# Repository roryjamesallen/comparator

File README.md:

# comparator
#### A simple dual comparator in Eurorack format.
  
Inputs between +12V and -12V can be compared, and an output of 0 or 5V will be produced accordingly, indicated by the LED.
  
The voltage to compare input A against is controlled by the knob, and is be default 0-12V. However, this voltage can be replaced by plugging a jack into input B, in which case the knob will attenuate this input.

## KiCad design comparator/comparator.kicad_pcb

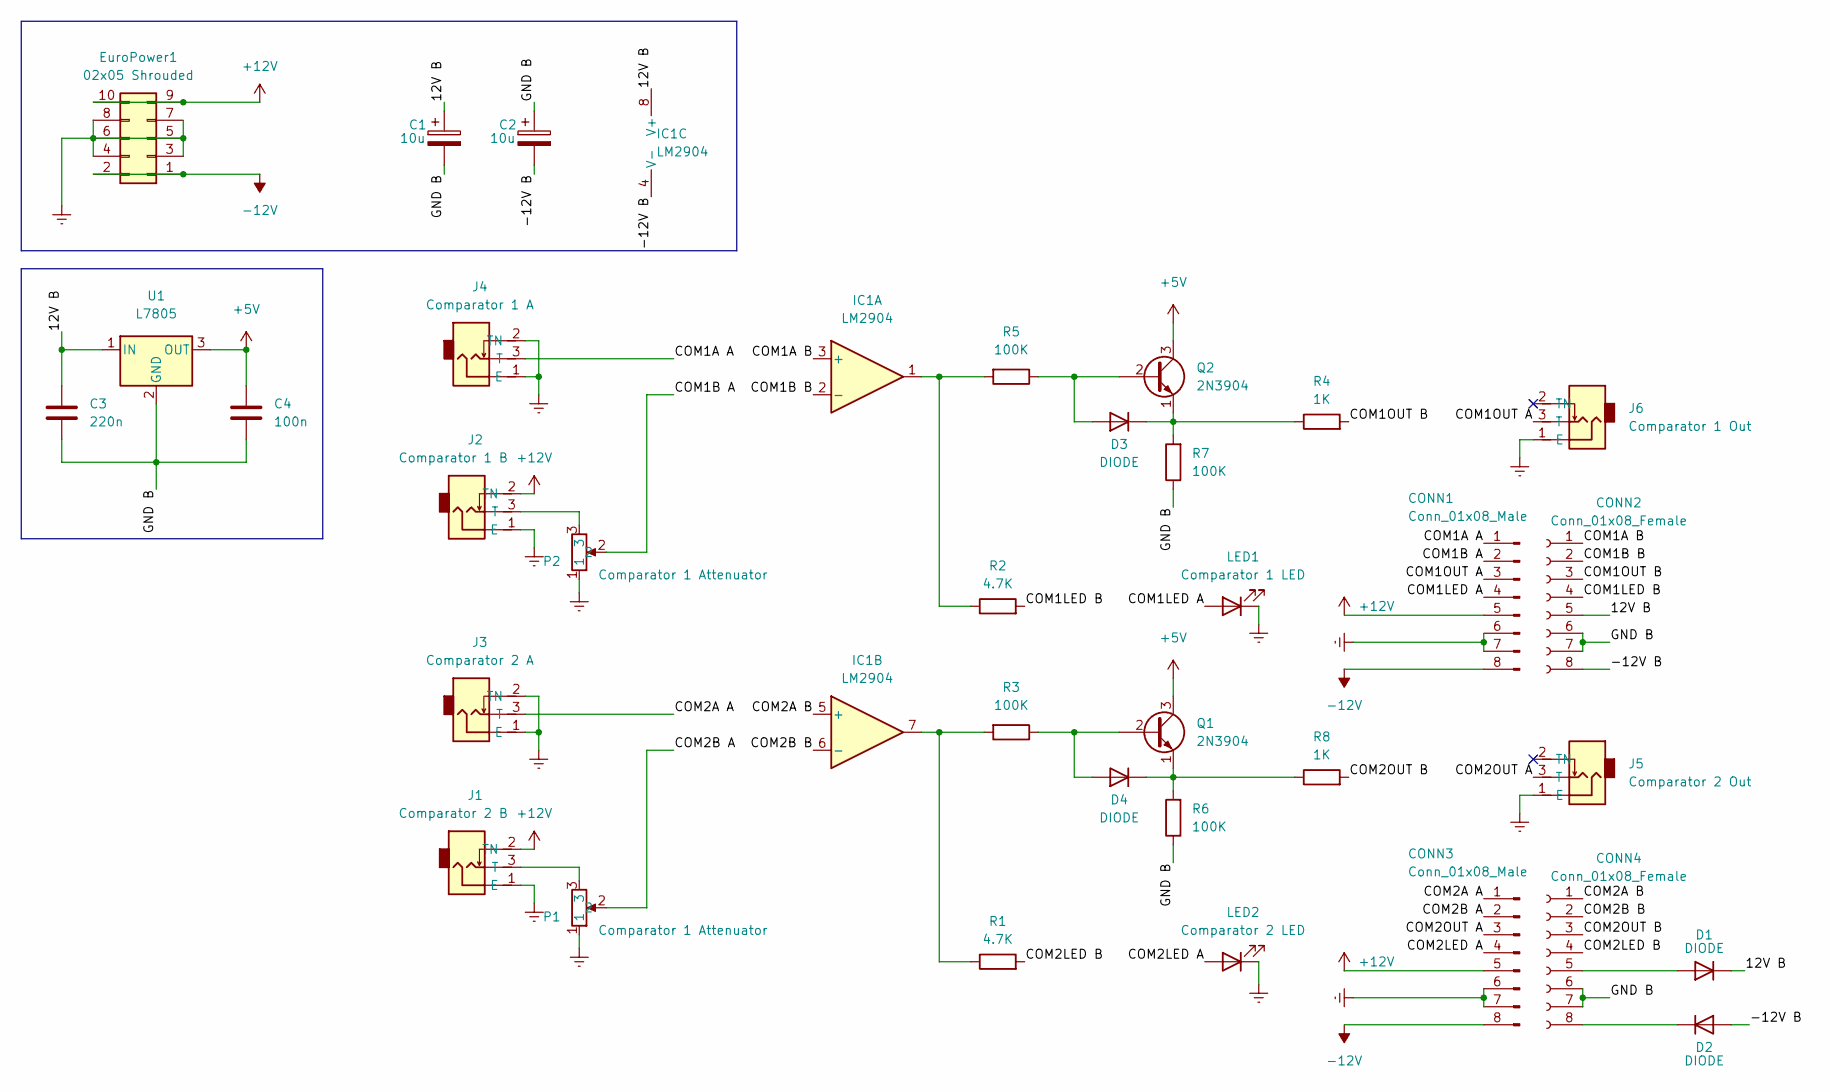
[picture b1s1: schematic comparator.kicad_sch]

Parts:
C1, C2: 10u; CP_Radial_D5.0mm_P2.50mm
C3: 220n; Capacitor Small Non-Polarised
C4: 100n; Capacitor Small Non-Polarised
CONN1, CONN3: Conn_01x08_Male; PinHeader_2x04_P2.54mm_Vertical
CONN2, CONN4: Conn_01x08_Female; PinSocket_2x04_P2.54mm_Vertical
D1, D2: DIODE; D_A-405_P7.62mm_Horizontal
D3, D4: DIODE; Schottky Diode
EuroPower1: 02x05 Shrouded; Eurorack Power Header Unlabeled
IC1: LM2904; DIP-8 IC Socket
J1: Comparator 2 B; Thonkiconn Mono Jack
J2: Comparator 1 B; Thonkiconn Mono Jack
J3: Comparator 2 A; Thonkiconn Mono Jack
J4: Comparator 1 A; Thonkiconn Mono Jack
J5: Comparator 2 Out; Thonkiconn Mono Jack
J6: Comparator 1 Out; Thonkiconn Mono Jack
LED1: Comparator 1 LED; LED 3mm
LED2: Comparator 2 LED; LED 3mm
P1, P2: Comparator 1 Attenuator; Potentiometer 9mm Vertical Linear
Q1, Q2: 2N3904; TO-92_Inline
R1, R2: 4.7K; Resistor 0.25W Through-Hole Short
R3, R5, R6, R7: 100K; Resistor 0.25W Through-Hole Short
R4, R8: 1K; Resistor 0.25W Through-Hole Short
U1: L7805; TO-92

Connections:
+5V: C4.1, Q1.3 (C), Q2.3 (C), U1.3 (OUT)
+12V: CONN1.5, CONN3.5, EuroPower1.9, EuroPower1.10, J1.2 (TN), J2.2 (TN)
-12V: CONN1.8, CONN3.8, EuroPower1.1, EuroPower1.2
/12V B: C1.1, C3.1, CONN2.5, D1.2 (K), IC1.8 (V+), U1.1 (IN)
/-12V B: C2.2, CONN2.8, D2.1 (A), IC1.4 (V-)
/COM1A A: CONN1.1, J4.3 (T)
/COM1A B: CONN2.1, IC1.3 (+)
/COM1B A: CONN1.2, P2.2
/COM1B B: CONN2.2, IC1.2 (-)
/COM1LED A: CONN1.4, LED1.2 (A)
/COM1LED B: CONN2.4, R2.2
/COM1OUT A: CONN1.3, J6.3 (T)
/COM1OUT B: CONN2.3, R4.2
/COM2A A: CONN3.1, J3.3 (T)
/COM2A B: CONN4.1, IC1.5 (+)
/COM2B A: CONN3.2, P1.2
/COM2B B: CONN4.2, IC1.6 (-)
/COM2LED A: CONN3.4, LED2.2 (A)
/COM2LED B: CONN4.4, R1.2
/COM2OUT A: CONN3.3, J5.3 (T)
/COM2OUT B: CONN4.3, R8.2
/GND B: C1.2, C2.1, C3.2, C4.2, CONN2.6, CONN2.7, CONN4.6, CONN4.7, R6.1, R7.1, U1.2 (GND)
Earth: CONN1.6, CONN1.7, CONN3.6, CONN3.7, EuroPower1.3, EuroPower1.4, EuroPower1.5, EuroPower1.6, EuroPower1.7, EuroPower1.8, J1.1 (E), J2.1 (E), J3.1 (E), J3.2 (TN), J4.1 (E), J4.2 (TN), J5.1 (E), J6.1 (E), LED1.1 (K), LED2.1 (K), P1.1, P2.1
unnamed: CONN4.5, D1.1 (A)
unnamed: CONN4.8, D2.2 (K)
unnamed: D3.1 (A), Q2.2 (B), R5.1
unnamed: D3.2 (K), Q2.1 (E), R4.1, R7.2
unnamed: D4.1 (A), Q1.2 (B), R3.1
unnamed: D4.2 (K), Q1.1 (E), R6.2, R8.1
unnamed: IC1.1, R2.1, R5.2
unnamed: IC1.7, R1.1, R3.2
unnamed: J1.3 (T), P1.3
unnamed: J2.3 (T), P2.3

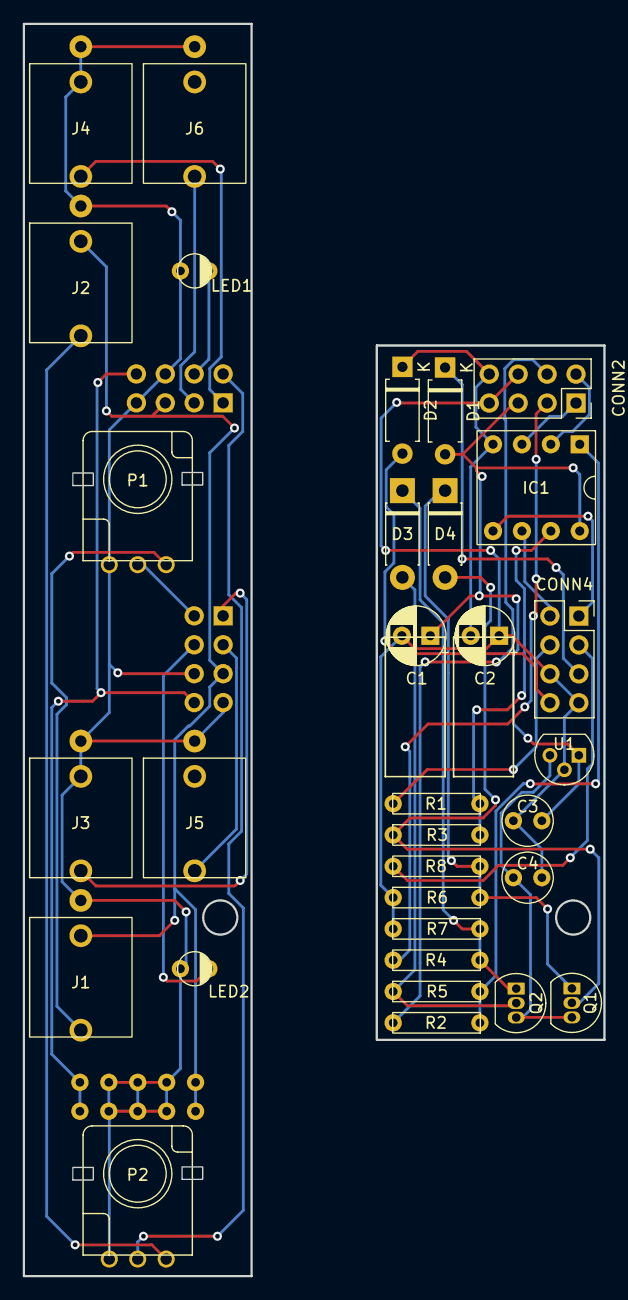
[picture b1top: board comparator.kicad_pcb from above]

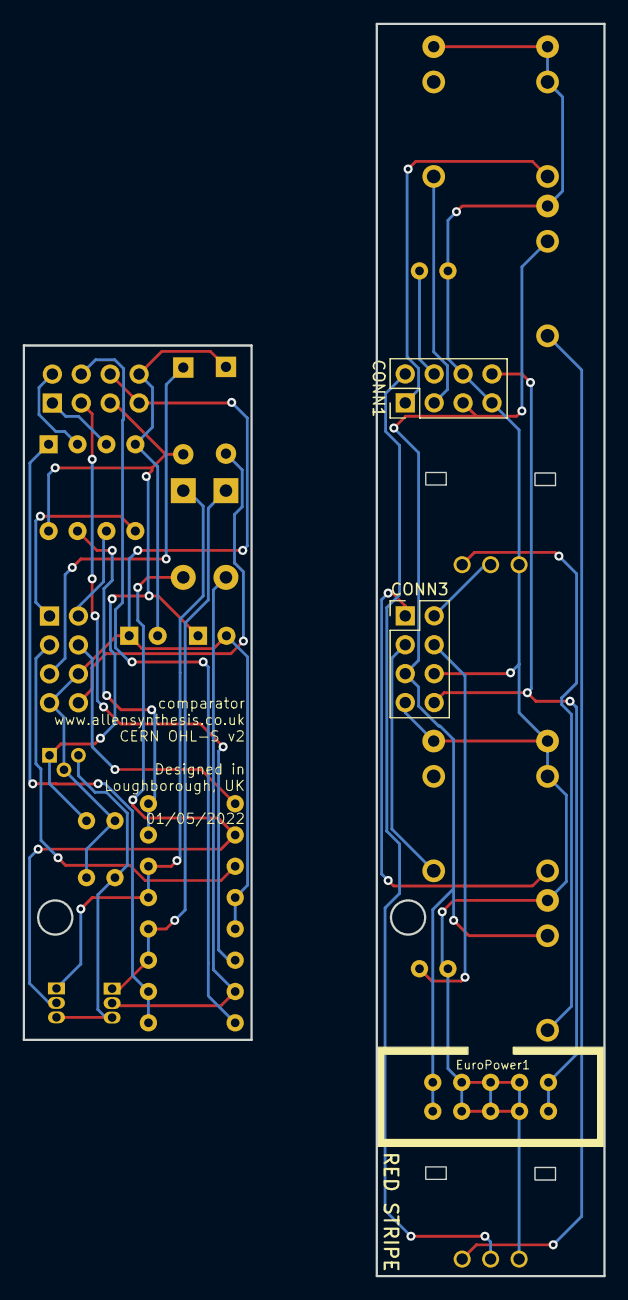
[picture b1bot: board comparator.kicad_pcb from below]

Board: 2 copper layers, 51.0 x 110.0 mm, 35 parts (3 on the bottom side), 33 nets.

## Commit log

2022-04-30 Create KiCad files
2022-05-01 KiCad changes
2022-05-01 3d model

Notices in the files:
comparator/comparator.kicad_pcb:
CERN OHL-S v2
